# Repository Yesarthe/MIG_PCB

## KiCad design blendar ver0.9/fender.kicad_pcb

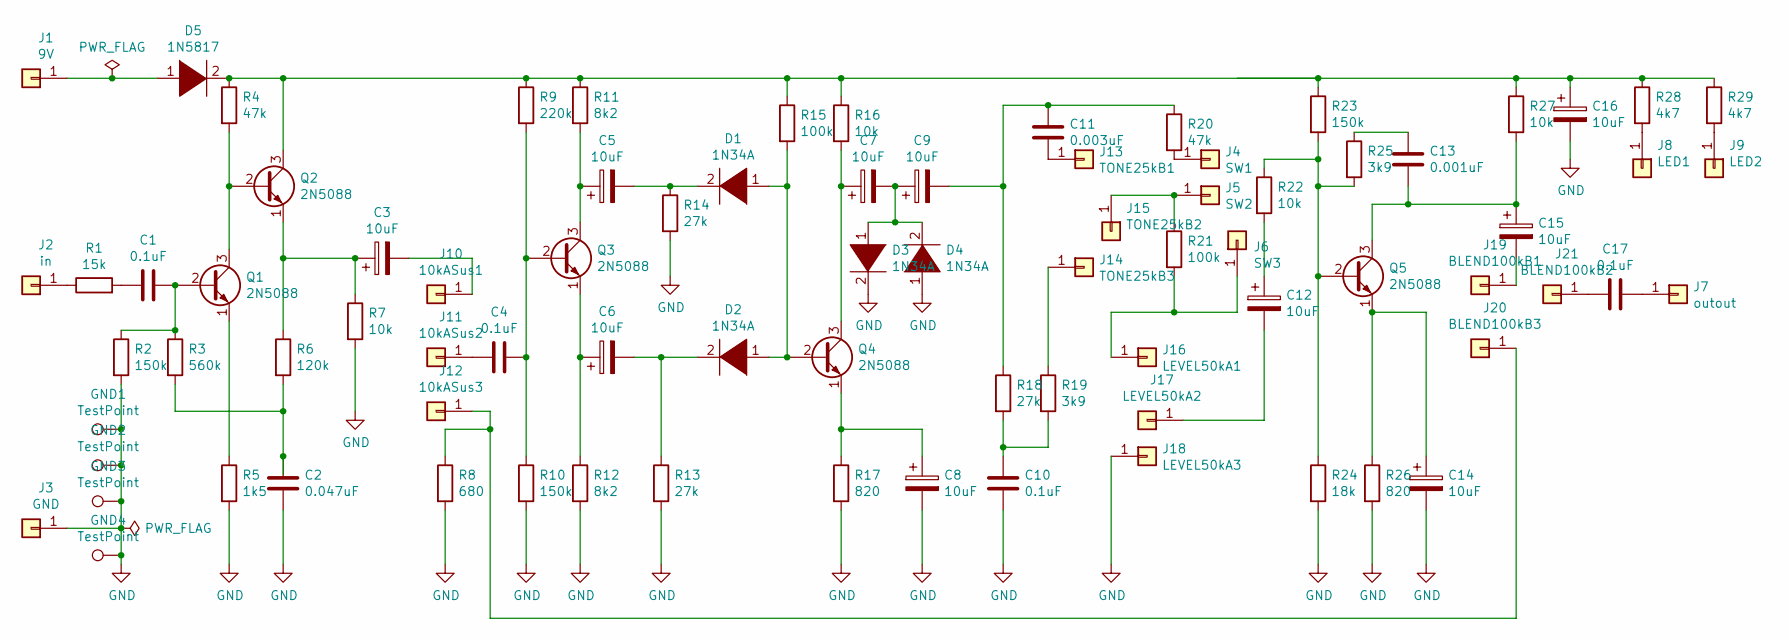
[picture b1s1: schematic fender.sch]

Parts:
C1, C4, C10, C17: 0.1uF; C_Disc_D3.0mm_W2.0mm_P2.50mm
C2: 0.047uF; C_Disc_D3.0mm_W2.0mm_P2.50mm
C3, C5, C6, C7, C8, C9, C12, C14, C15, C16: 10uF; CP_Radial_D5.0mm_P2.50mm
C11: 0.003uF; C_Disc_D3.0mm_W2.0mm_P2.50mm
C13: 0.001uF; C_Disc_D3.0mm_W2.0mm_P2.50mm
D1, D2, D3, D4: 1N34A; D_DO-35_SOD27_P10.16mm_Horizontal
D5: 1N5817; D_DO-35_SOD27_P10.16mm_Horizontal
GND1, GND2, GND3, GND4: TestPoint; TestPoint_THTPad_D2.5mm_Drill1.2mm
J1: 9V; TestPoint_THTPad_D2.5mm_Drill1.2mm
J2: in; TestPoint_THTPad_D2.5mm_Drill1.2mm
J3: GND; TestPoint_THTPad_D2.5mm_Drill1.2mm
J4: SW1; TestPoint_THTPad_D2.5mm_Drill1.2mm
J5: SW2; TestPoint_THTPad_D2.5mm_Drill1.2mm
J6: SW3; TestPoint_THTPad_D2.5mm_Drill1.2mm
J7: outout; TestPoint_THTPad_D2.5mm_Drill1.2mm
J8: LED1; TestPoint_THTPad_D2.5mm_Drill1.2mm
J9: LED2; TestPoint_THTPad_D2.5mm_Drill1.2mm
J10: 10kASus1; TestPoint_THTPad_D2.5mm_Drill1.2mm
J11: 10kASus2; TestPoint_THTPad_D2.5mm_Drill1.2mm
J12: 10kASus3; TestPoint_THTPad_D2.5mm_Drill1.2mm
J13: TONE25kB1; TestPoint_THTPad_D2.5mm_Drill1.2mm
J14: TONE25kB3; TestPoint_THTPad_D2.5mm_Drill1.2mm
J15: TONE25kB2; TestPoint_THTPad_D2.5mm_Drill1.2mm
J16: LEVEL50kA1; TestPoint_THTPad_D2.5mm_Drill1.2mm
J17: LEVEL50kA2; TestPoint_THTPad_D2.5mm_Drill1.2mm
J18: LEVEL50kA3; TestPoint_THTPad_D2.5mm_Drill1.2mm
J19: BLEND100kB1; TestPoint_THTPad_D2.5mm_Drill1.2mm
J20: BLEND100kB3; TestPoint_THTPad_D2.5mm_Drill1.2mm
J21: BLEND100kB2; TestPoint_THTPad_D2.5mm_Drill1.2mm
Q1, Q2, Q3, Q4, Q5: 2N5088; TO-92_Inline
R1: 15k; R_Axial_DIN0207_L6.3mm_D2.5mm_P7.62mm_Horizontal
R2, R10, R23: 150k; R_Axial_DIN0207_L6.3mm_D2.5mm_P7.62mm_Horizontal
R3: 560k; R_Axial_DIN0207_L6.3mm_D2.5mm_P7.62mm_Horizontal
R4, R20: 47k; R_Axial_DIN0207_L6.3mm_D2.5mm_P7.62mm_Horizontal
R5: 1k5; R_Axial_DIN0207_L6.3mm_D2.5mm_P7.62mm_Horizontal
R6: 120k; R_Axial_DIN0207_L6.3mm_D2.5mm_P7.62mm_Horizontal
R7, R16, R22, R27: 10k; R_Axial_DIN0207_L6.3mm_D2.5mm_P7.62mm_Horizontal
R8: 680; R_Axial_DIN0207_L6.3mm_D2.5mm_P7.62mm_Horizontal
R9: 220k; R_Axial_DIN0207_L6.3mm_D2.5mm_P7.62mm_Horizontal
R11, R12: 8k2; R_Axial_DIN0207_L6.3mm_D2.5mm_P7.62mm_Horizontal
R13, R14, R18: 27k; R_Axial_DIN0207_L6.3mm_D2.5mm_P7.62mm_Horizontal
R15, R21: 100k; R_Axial_DIN0207_L6.3mm_D2.5mm_P7.62mm_Horizontal
R17, R26: 820; R_Axial_DIN0207_L6.3mm_D2.5mm_P7.62mm_Horizontal
R19, R25: 3k9; R_Axial_DIN0207_L6.3mm_D2.5mm_P7.62mm_Horizontal
R24: 18k; R_Axial_DIN0207_L6.3mm_D2.5mm_P7.62mm_Horizontal
R28, R29: 4k7; R_Axial_DIN0207_L6.3mm_D2.5mm_P7.62mm_Horizontal

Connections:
GND: C2.2, C8.2, C10.2, C14.2, C16.2, D3.2 (A), D4.1 (K), GND1.1, GND2.1, GND3.1, GND4.1, J3.1, J18.1, R2.2, R5.2, R7.2, R8.2, R10.2, R12.2, R13.2, R14.2, R17.2, R24.2, R26.2
unnamed: C1.1, Q1.2 (B), R2.1, R3.1
unnamed: C1.2, R1.2
unnamed: C2.1, R3.2, R6.2
unnamed: C3.1, Q2.1 (E), R6.1, R7.1
unnamed: C3.2, J10.1
unnamed: C4.1, Q3.2 (B), R9.2, R10.1
unnamed: C4.2, J11.1
unnamed: C5.1, Q3.3 (C), R11.2
unnamed: C5.2, D1.2 (A), R14.1
unnamed: C6.1, Q3.1 (E), R12.1
unnamed: C6.2, D2.2 (A), R13.1
unnamed: C7.1, Q4.3 (C), R16.2
unnamed: C7.2, C9.1, D3.1 (K), D4.2 (A)
unnamed: C8.1, Q4.1 (E), R17.1
unnamed: C10.1, R18.2, R19.2
unnamed: C9.2, C11.1, R18.1, R20.1
unnamed: C11.2, J13.1
unnamed: C12.1, R22.2
unnamed: C12.2, J17.1
unnamed: C13.1, R25.1
unnamed: C13.2, C15.1, Q5.3 (C), R27.2
unnamed: C14.1, Q5.1 (E), R26.1
unnamed: C15.2, J19.1
unnamed: C16.1, D5.2 (A), Q2.3 (C), R4.1, R9.1, R11.1, R15.1, R16.1, R23.1, R27.1, R28.1, R29.1
unnamed: C17.1, J7.1
unnamed: C17.2, J21.1
unnamed: D1.1 (K), D2.1 (K), Q4.2 (B), R15.2
unnamed: D5.1 (K), J1.1
unnamed: J2.1, R1.1
unnamed: J4.1, R20.2
unnamed: J8.1, R28.2
unnamed: J9.1, R29.2
unnamed: J12.1, J20.1, R8.1
unnamed: J14.1, R19.1
unnamed: J5.1, J15.1, R21.1
unnamed: J6.1, J16.1, R21.2
unnamed: Q1.1 (E), R5.1
unnamed: Q1.3 (C), Q2.2 (B), R4.2
unnamed: Q5.2 (B), R22.1, R23.2, R24.1, R25.2

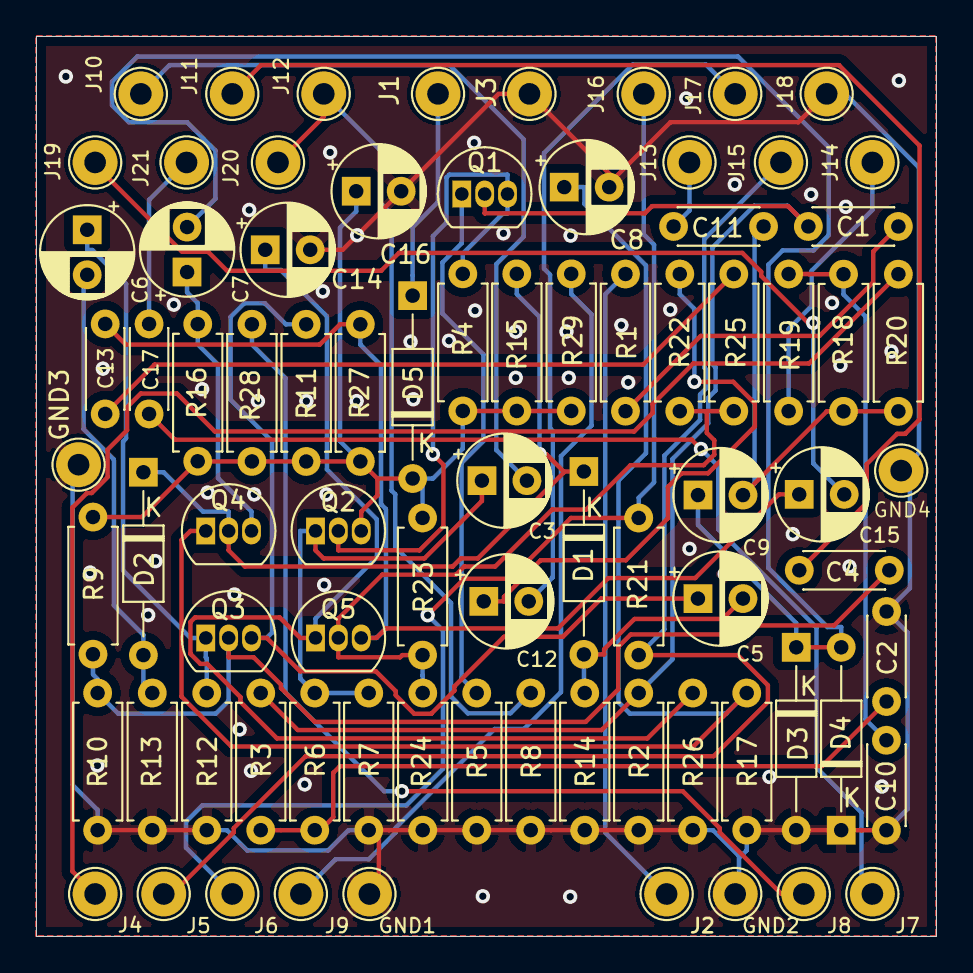
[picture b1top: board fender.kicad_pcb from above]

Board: 2 copper layers, 50.0 x 50.0 mm, 81 parts (0 on the bottom side), 40 nets.

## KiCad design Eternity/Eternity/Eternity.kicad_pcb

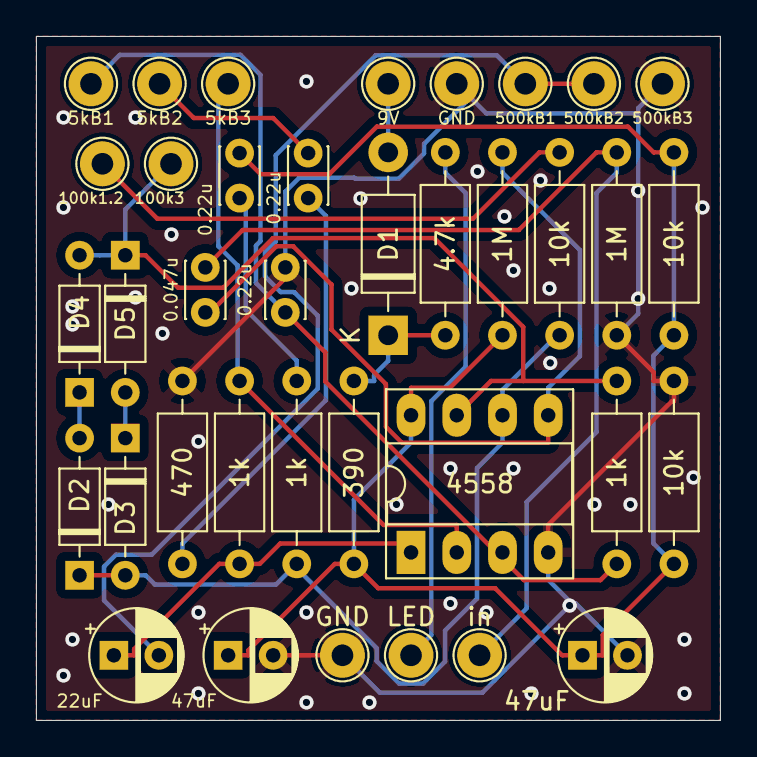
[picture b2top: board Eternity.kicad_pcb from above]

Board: 2 copper layers, 38.0 x 38.0 mm, 37 parts (0 on the bottom side), 19 nets.

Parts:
0.22u, 0.22u#2: 0.22u; C_Disc_D3.0mm_W2.0mm_P2.50mm
0.22u#3: 0.22uF; C_Disc_D3.0mm_W2.0mm_P2.50mm
0.047u: 0.047u; C_Disc_D3.0mm_W2.0mm_P2.50mm
1M, 1M#2: 1M; R_Axial_DIN0207_L6.3mm_D2.5mm_P10.16mm_Horizontal
1k, 1k#2, 1k#3: 1k; R_Axial_DIN0207_L6.3mm_D2.5mm_P10.16mm_Horizontal
4.7k: R; R_Axial_DIN0207_L6.3mm_D2.5mm_P10.16mm_Horizontal
5kB1: Tone_5kB1; TestPoint_THTPad_D2.5mm_Drill1.2mm
5kB2: Tone_5kB2; TestPoint_THTPad_D2.5mm_Drill1.2mm
5kB3: Tone_5kB3; TestPoint_THTPad_D2.5mm_Drill1.2mm
9V: Conn_01x01; TestPoint_THTPad_D2.5mm_Drill1.2mm
10k, 10k#2, 10k#3: 10k; R_Axial_DIN0207_L6.3mm_D2.5mm_P10.16mm_Horizontal
22uF: 22uF; CP_Radial_D5.0mm_P2.50mm
47uF, 47uF#2: 47u; CP_Radial_D5.0mm_P2.50mm
100k1.2: Drive100k1_2; TestPoint_THTPad_D2.5mm_Drill1.2mm
100k3: Drive100k3; TestPoint_THTPad_D2.5mm_Drill1.2mm
390: 390; R_Axial_DIN0207_L6.3mm_D2.5mm_P10.16mm_Horizontal
470: 470; R_Axial_DIN0207_L6.3mm_D2.5mm_P10.16mm_Horizontal
500kB1: Vol500B1; TestPoint_THTPad_D2.5mm_Drill1.2mm
500kB2: Vol500B2_OUT; TestPoint_THTPad_D2.5mm_Drill1.2mm
500kB3: Vol500B3; TestPoint_THTPad_D2.5mm_Drill1.2mm
4558: RC4558; DIP-8_W7.62mm_Socket_LongPads
D1: 1N5817; D_DO-41_SOD81_P10.16mm_Horizontal
D2, D3, D4, D5: 1N4148; D_DO-35_SOD27_P7.62mm_Horizontal
GND: in_GND; TestPoint_THTPad_D2.5mm_Drill1.2mm
GND#2: in_GND; TestPoint_THTPad_D2.5mm_Drill1.2mm
LED: LED1; TestPoint_THTPad_D2.5mm_Drill1.2mm
in: in; TestPoint_THTPad_D2.5mm_Drill1.2mm

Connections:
GND: 0.22u#2.2, 1M.1, 10k#2.2, 47uF.2, 47uF#2.2, 470.1, 500kB3.1, 4558.4, GND.1, GND#2.1
unnamed: 9V.1, D1.2
unnamed: 0.22u.2, 1M#2.1, 10k.1, 10k.2, 10k#2.1, 47uF.1, 47uF#2.1, 390.1, 4558.8
unnamed: 0.22u.1, 1k.2
unnamed: 0.047u.1, 1M#2.2, 4558.5
unnamed: 0.047u.2, 1M.2, in.1
unnamed: 0.22u#2.1, 1k#2.1, 5kB1.1, 4558.3
unnamed: 1k#3.2, 22uF.1, 4558.1
unnamed: 22uF.2, 500kB1.1, 500kB2.1
unnamed: 0.22u#3.1, 470.2
unnamed: 0.22u#3.2, 5kB2.1
unnamed: 4.7k.1, 390.2, D1.1
unnamed: 1k.1, 10k#3.1, 4558.6, D2.1, D3.2
unnamed: D2.2, D4.1
unnamed: D3.1, D5.2
unnamed: 1k#2.2, 100k3.1, 4558.7, D4.2, D5.1
unnamed: 10k#3.2, 100k1.2.1
unnamed: 1k#3.1, 5kB3.1, 4558.2
unnamed: 4.7k.2, LED.1

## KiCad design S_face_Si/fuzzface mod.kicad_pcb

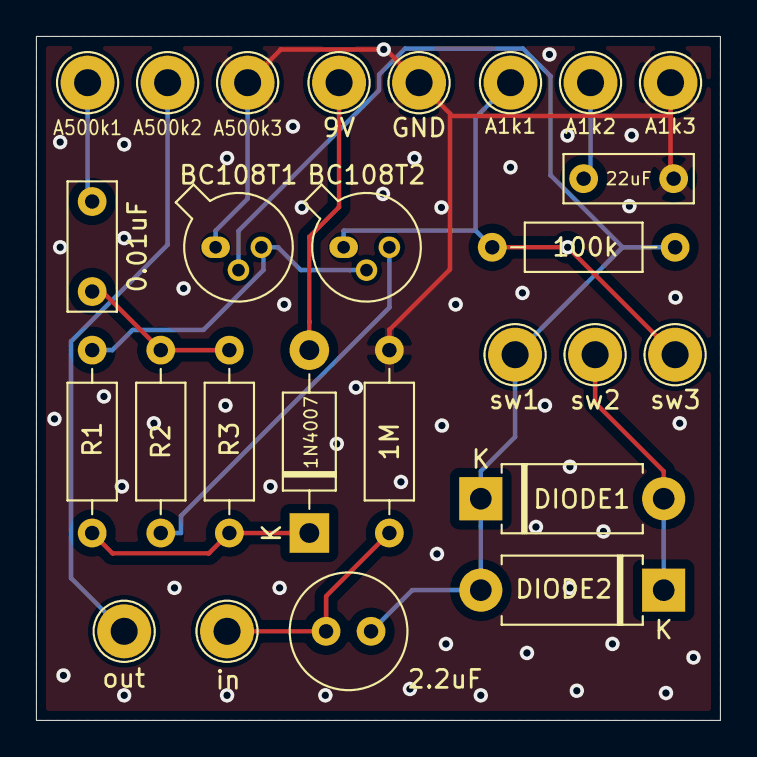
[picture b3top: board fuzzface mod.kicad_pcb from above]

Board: 2 copper layers, 38.0 x 38.0 mm, 26 parts (0 on the bottom side), 13 nets.

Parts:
0.01uF: 0.01uF; C_Rect_L7.0mm_W2.5mm_P5.00mm
1M: 1M; R_Axial_DIN0207_L6.3mm_D2.5mm_P10.16mm_Horizontal
1N4007: 1N4007; D_DO-41_SOD81_P10.16mm_Horizontal
2.2uF: 2.2uF; C_Radial_D6.3mm_H5.0mm_P2.50mm
9V: 9V; TestPoint_Loop_D2.54mm_Drill1.5mm_Beaded
22uF: 22uF; C_Rect_L7.0mm_W2.5mm_P5.00mm
100k: 100k; R_Axial_DIN0207_L6.3mm_D2.5mm_P10.16mm_Horizontal
A1k1: A1k1; TestPoint_Loop_D2.54mm_Drill1.5mm_Beaded
A1k2: A1k2; TestPoint_Loop_D2.54mm_Drill1.5mm_Beaded
A1k3: A1k3; TestPoint_Loop_D2.54mm_Drill1.5mm_Beaded
A500k1: A500k1; TestPoint_Loop_D2.54mm_Drill1.5mm_Beaded
A500k2: A500k2; TestPoint_Loop_D2.54mm_Drill1.5mm_Beaded
A500k3: A500k3; TestPoint_Loop_D2.54mm_Drill1.5mm_Beaded
BC108T1, BC108T2: BC108; TO-18-3
DIODE1, DIODE2: DIODE; D_DO-15_P10.16mm_Horizontal
GND: GND; TestPoint_Loop_D2.54mm_Drill1.5mm_Beaded
R1: R1; R_Axial_DIN0207_L6.3mm_D2.5mm_P10.16mm_Horizontal
R2: R2; R_Axial_DIN0207_L6.3mm_D2.5mm_P10.16mm_Horizontal
R3: R3; R_Axial_DIN0207_L6.3mm_D2.5mm_P10.16mm_Horizontal
in: in; TestPoint_Loop_D2.54mm_Drill1.5mm_Beaded
out: out; TestPoint_Loop_D2.54mm_Drill1.5mm_Beaded
sw1: sw1; TestPoint_Loop_D2.54mm_Drill1.5mm_Beaded
sw2: sw2; TestPoint_Loop_D2.54mm_Drill1.5mm_Beaded
sw3: sw3; TestPoint_Loop_D2.54mm_Drill1.5mm_Beaded

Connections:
GND: 1M.2, 22uF.2, A1k3.1, A500k3.1, BC108T1.1, GND.1
unnamed: 0.01uF.1, A500k1.1
unnamed: 0.01uF.2, R2.1, R3.2
unnamed: 1M.1, 2.2uF.2, in.1
unnamed: 1N4007.1, R1.1, R3.1
unnamed: 1N4007.2, 9V.1
unnamed: 22uF.1, A1k2.1
unnamed: 100k.1, A1k1.1, BC108T2.1, sw3.1
unnamed: 2.2uF.1, 100k.2, BC108T1.2, DIODE1.1, DIODE2.2, sw1.1
unnamed: A500k2.1, out.1
unnamed: BC108T1.3, BC108T2.2, R1.2
unnamed: BC108T2.3, R2.2
unnamed: DIODE1.2, DIODE2.1, sw2.1

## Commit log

2021-08-09 eternity ver1.0
    sd
